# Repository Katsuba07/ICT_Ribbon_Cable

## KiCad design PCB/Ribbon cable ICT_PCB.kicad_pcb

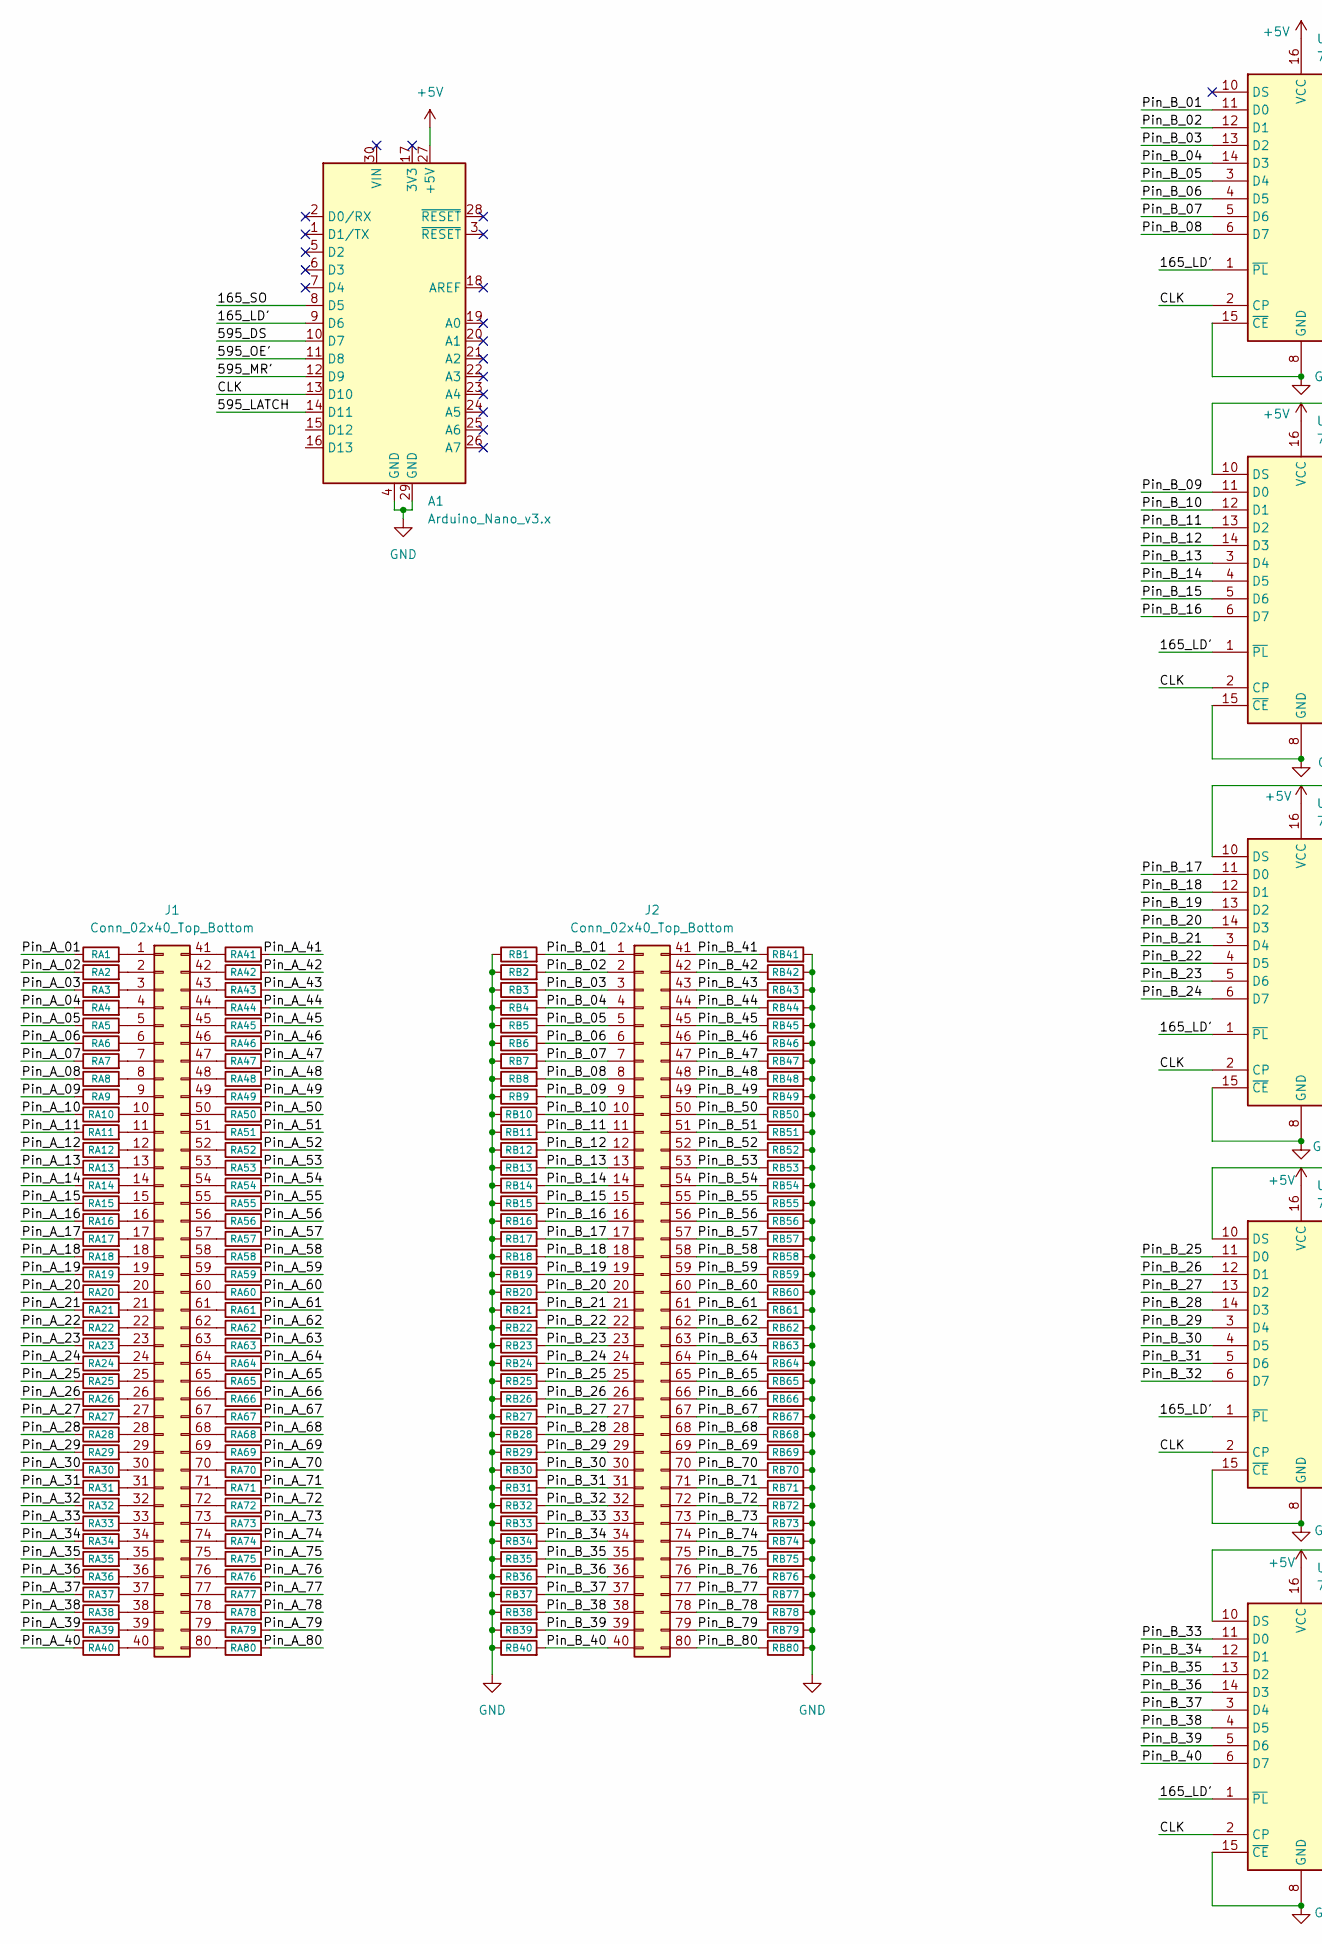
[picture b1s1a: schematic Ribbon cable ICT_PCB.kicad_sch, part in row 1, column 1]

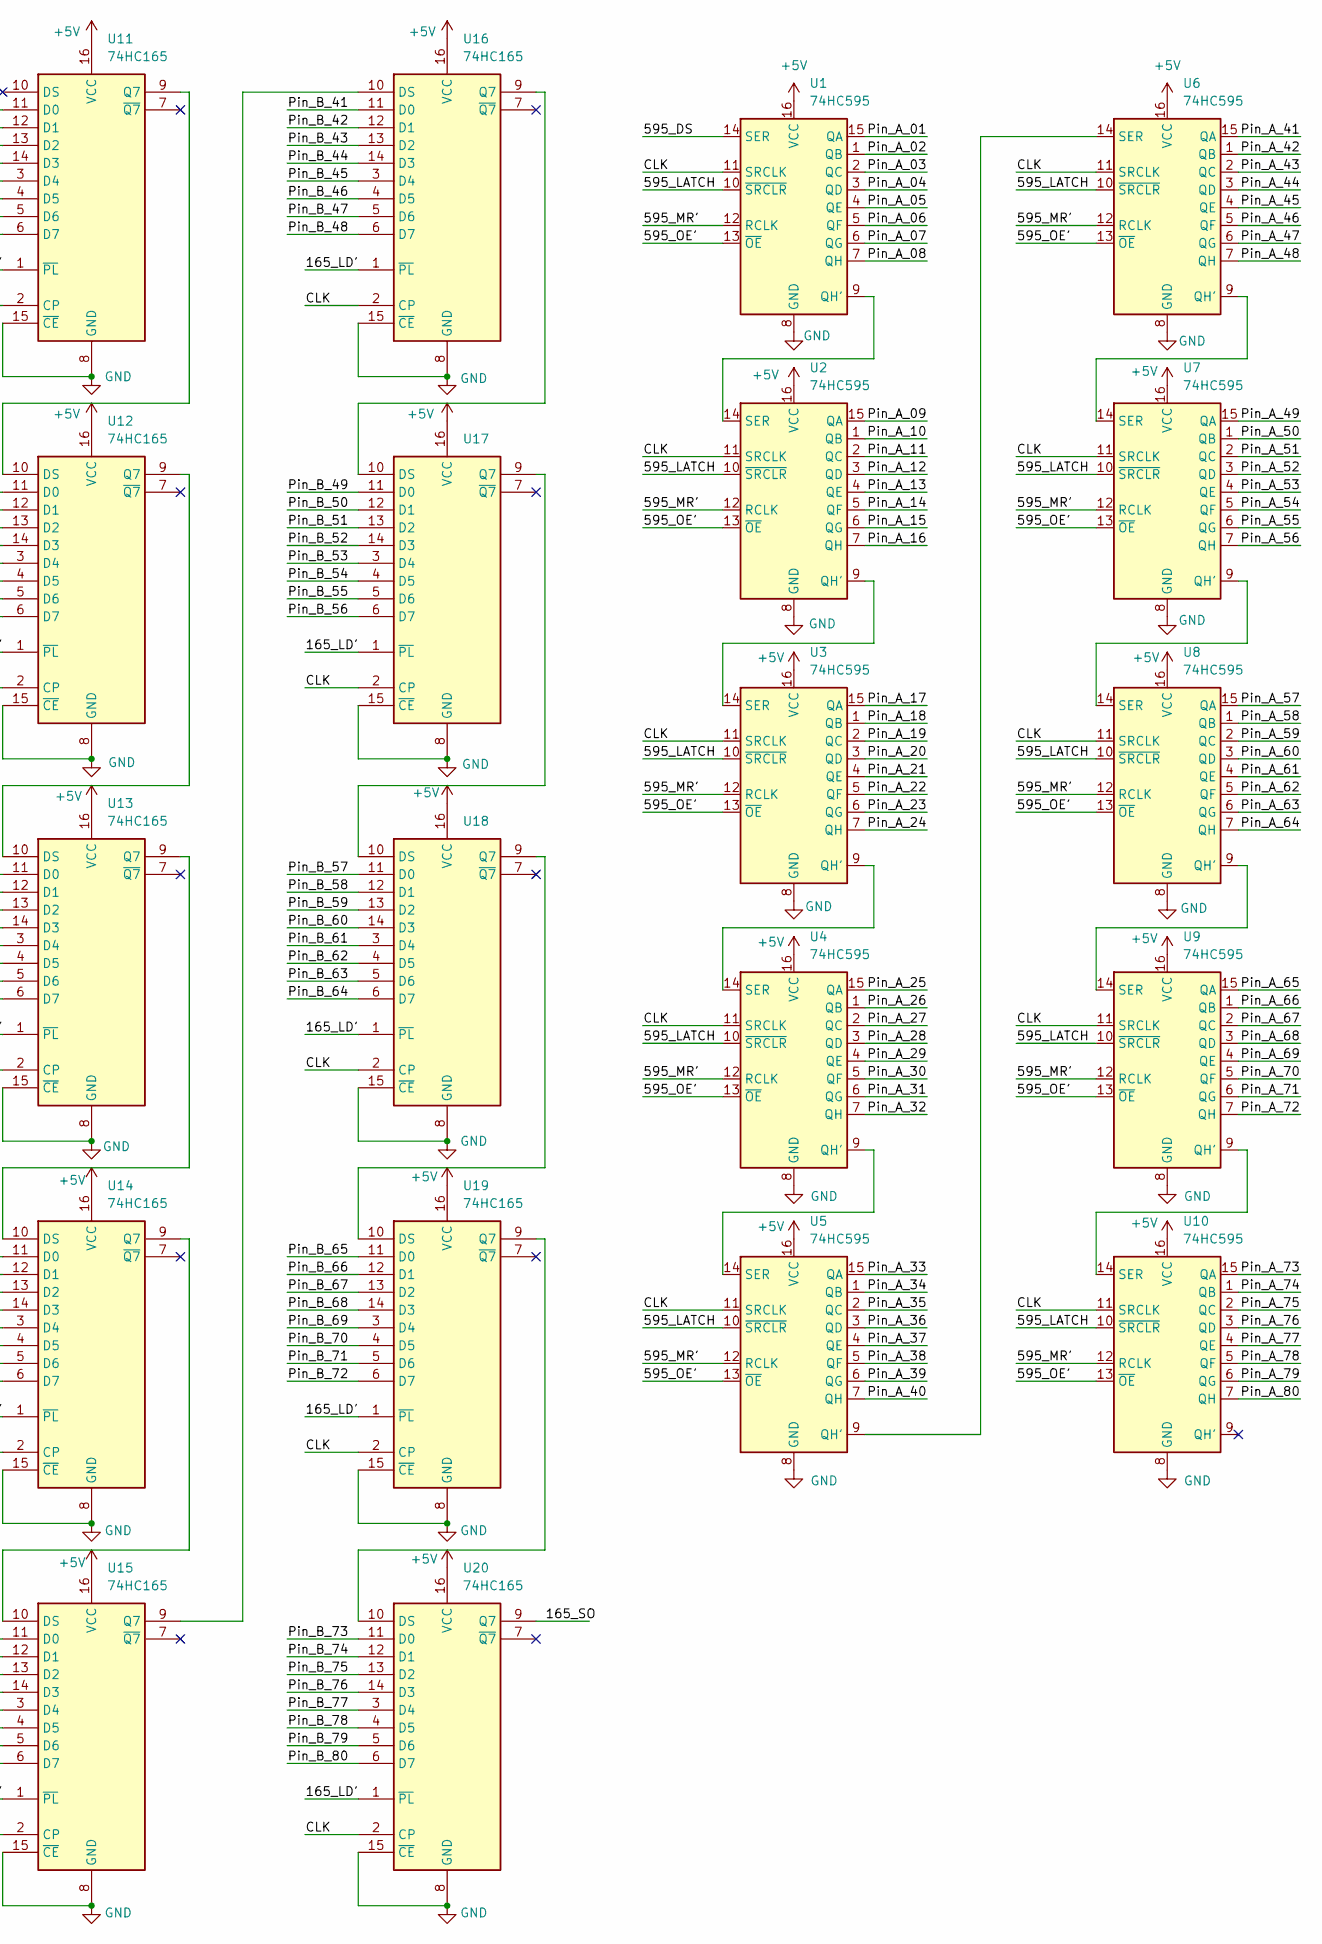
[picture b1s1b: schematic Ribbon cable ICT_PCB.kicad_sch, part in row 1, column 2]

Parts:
A1: Arduino_Nano_v3.x; Arduino_Nano
J1, J2: Conn_02x40_Top_Bottom; PinSocket_2x40_P2.54mm_Vertical
RA1, RA2, RA3, RA4, RA5, RA6, RA7, RA8, RA9, RA10, RA11, RA12, RA13, RA14, RA15, RA16, RA17, RA18, RA19, RA20, RA21, RA22, RA23, RA24, RA25, RA26, RA27, RA28, RA29, RA30, RA31, RA32, RA33, RA34, RA35, RA36, RA37, RA38, RA39, RA40, RA41, RA42, RA43, RA44, RA45, RA46, RA47, RA48, RA49, RA50, RA51, RA52, RA53, RA54, RA55, RA56, RA57, RA58, RA59, RA60, RA61, RA62, RA63, RA64, RA65, RA66, RA67, RA68, RA69, RA70, RA71, RA72, RA73, RA74, RA75, RA76, RA77, RA78, RA79, RA80: R; R_0603_1608Metric
RB1, RB2, RB3, RB4, RB5, RB6, RB7, RB8, RB9, RB10, RB11, RB12, RB13, RB14, RB15, RB16, RB17, RB18, RB19, RB20, RB21, RB22, RB23, RB24, RB25, RB26, RB27, RB28, RB29, RB30, RB31, RB32, RB33, RB34, RB35, RB36, RB37, RB38, RB39, RB40, RB41, RB42, RB43, RB44, RB45, RB46, RB47, RB48, RB49, RB50, RB51, RB52, RB53, RB54, RB55, RB56, RB57, RB58, RB59, RB60, RB61, RB62, RB63, RB64, RB65, RB66, RB67, RB68, RB69, RB70, RB71, RB72, RB73, RB74, RB75, RB76, RB77, RB78, RB79, RB80: R; R_0603_1608Metric
U1, U2, U3, U4, U5, U6, U7, U8, U9, U10: 74HC595; SOIC-16_3.9x9.9mm_P1.27mm
U11, U12, U13, U14, U15, U16, U17, U18, U19, U20: 74HC165; SOIC-16_3.9x9.9mm_P1.27mm

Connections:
+5V: A1.27 (+5V), U1.16 (VCC), U2.16 (VCC), U3.16 (VCC), U4.16 (VCC), U5.16 (VCC), U6.16 (VCC), U7.16 (VCC), U8.16 (VCC), U9.16 (VCC), U10.16 (VCC), U11.16 (VCC), U12.16 (VCC), U13.16 (VCC), U14.16 (VCC), U15.16 (VCC), U16.16 (VCC), U17.16 (VCC), U18.16 (VCC), U19.16 (VCC), U20.16 (VCC)
/165_LD': A1.9 (D6), U11.1 (~PL), U12.1 (~PL), U13.1 (~PL), U14.1 (~PL), U15.1 (~PL), U16.1 (~PL), U17.1 (~PL), U18.1 (~PL), U19.1 (~PL), U20.1 (~PL)
/165_SO: A1.8 (D5), U20.9 (Q7)
/595_DS: A1.10 (D7), U1.14 (SER)
/595_LATCH: A1.14 (D11), U1.10 (~SRCLR), U2.10 (~SRCLR), U3.10 (~SRCLR), U4.10 (~SRCLR), U5.10 (~SRCLR), U6.10 (~SRCLR), U7.10 (~SRCLR), U8.10 (~SRCLR), U9.10 (~SRCLR), U10.10 (~SRCLR)
/595_MR': A1.12 (D9), U1.12 (RCLK), U2.12 (RCLK), U3.12 (RCLK), U4.12 (RCLK), U5.12 (RCLK), U6.12 (RCLK), U7.12 (RCLK), U8.12 (RCLK), U9.12 (RCLK), U10.12 (RCLK)
/595_OE': A1.11 (D8), U1.13 (~OE), U2.13 (~OE), U3.13 (~OE), U4.13 (~OE), U5.13 (~OE), U6.13 (~OE), U7.13 (~OE), U8.13 (~OE), U9.13 (~OE), U10.13 (~OE)
/CLK: A1.13 (D10), U1.11 (SRCLK), U2.11 (SRCLK), U3.11 (SRCLK), U4.11 (SRCLK), U5.11 (SRCLK), U6.11 (SRCLK), U7.11 (SRCLK), U8.11 (SRCLK), U9.11 (SRCLK), U10.11 (SRCLK), U11.2 (CP), U12.2 (CP), U13.2 (CP), U14.2 (CP), U15.2 (CP), U16.2 (CP), U17.2 (CP), U18.2 (CP), U19.2 (CP), U20.2 (CP)
/Pin_A_01: RA1.1, U1.15 (QA)
/Pin_A_02: RA2.1, U1.1 (QB)
/Pin_A_03: RA3.1, U1.2 (QC)
/Pin_A_04: RA4.1, U1.3 (QD)
/Pin_A_05: RA5.1, U1.4 (QE)
/Pin_A_06: RA6.1, U1.5 (QF)
/Pin_A_07: RA7.1, U1.6 (QG)
/Pin_A_08: RA8.1, U1.7 (QH)
/Pin_A_09: RA9.1, U2.15 (QA)
/Pin_A_10: RA10.1, U2.1 (QB)
/Pin_A_11: RA11.1, U2.2 (QC)
/Pin_A_12: RA12.1, U2.3 (QD)
/Pin_A_13: RA13.1, U2.4 (QE)
/Pin_A_14: RA14.1, U2.5 (QF)
/Pin_A_15: RA15.1, U2.6 (QG)
/Pin_A_16: RA16.1, U2.7 (QH)
/Pin_A_17: RA17.1, U3.15 (QA)
/Pin_A_18: RA18.1, U3.1 (QB)
/Pin_A_19: RA19.1, U3.2 (QC)
/Pin_A_20: RA20.1, U3.3 (QD)
/Pin_A_21: RA21.1, U3.4 (QE)
/Pin_A_22: RA22.1, U3.5 (QF)
/Pin_A_23: RA23.1, U3.6 (QG)
/Pin_A_24: RA24.1, U3.7 (QH)
/Pin_A_25: RA25.1, U4.15 (QA)
/Pin_A_26: RA26.1, U4.1 (QB)
/Pin_A_27: RA27.1, U4.2 (QC)
/Pin_A_28: RA28.1, U4.3 (QD)
/Pin_A_29: RA29.1, U4.4 (QE)
/Pin_A_30: RA30.1, U4.5 (QF)
/Pin_A_31: RA31.1, U4.6 (QG)
/Pin_A_32: RA32.1, U4.7 (QH)
/Pin_A_33: RA33.1, U5.15 (QA)
/Pin_A_34: RA34.1, U5.1 (QB)
/Pin_A_35: RA35.1, U5.2 (QC)
/Pin_A_36: RA36.1, U5.3 (QD)
/Pin_A_37: RA37.1, U5.4 (QE)
/Pin_A_38: RA38.1, U5.5 (QF)
/Pin_A_39: RA39.1, U5.6 (QG)
/Pin_A_40: RA40.1, U5.7 (QH)
/Pin_A_41: RA41.2, U6.15 (QA)
/Pin_A_42: RA42.2, U6.1 (QB)
/Pin_A_43: RA43.2, U6.2 (QC)
/Pin_A_44: RA44.2, U6.3 (QD)
/Pin_A_45: RA45.2, U6.4 (QE)
/Pin_A_46: RA46.2, U6.5 (QF)
/Pin_A_47: RA47.2, U6.6 (QG)
/Pin_A_48: RA48.2, U6.7 (QH)
/Pin_A_49: RA49.2, U7.15 (QA)
/Pin_A_50: RA50.2, U7.1 (QB)
/Pin_A_51: RA51.2, U7.2 (QC)
/Pin_A_52: RA52.2, U7.3 (QD)
/Pin_A_53: RA53.2, U7.4 (QE)
/Pin_A_54: RA54.2, U7.5 (QF)
/Pin_A_55: RA55.2, U7.6 (QG)
/Pin_A_56: RA56.2, U7.7 (QH)
/Pin_A_57: RA57.2, U8.15 (QA)
/Pin_A_58: RA58.2, U8.1 (QB)
/Pin_A_59: RA59.2, U8.2 (QC)
/Pin_A_60: RA60.2, U8.3 (QD)
/Pin_A_61: RA61.2, U8.4 (QE)
/Pin_A_62: RA62.2, U8.5 (QF)
/Pin_A_63: RA63.2, U8.6 (QG)
/Pin_A_64: RA64.2, U8.7 (QH)
/Pin_A_65: RA65.2, U9.15 (QA)
/Pin_A_66: RA66.2, U9.1 (QB)
/Pin_A_67: RA67.2, U9.2 (QC)
/Pin_A_68: RA68.2, U9.3 (QD)
/Pin_A_69: RA69.2, U9.4 (QE)
/Pin_A_70: RA70.2, U9.5 (QF)
/Pin_A_71: RA71.2, U9.6 (QG)
/Pin_A_72: RA72.2, U9.7 (QH)
/Pin_A_73: RA73.2, U10.15 (QA)
/Pin_A_74: RA74.2, U10.1 (QB)
/Pin_A_75: RA75.2, U10.2 (QC)
/Pin_A_76: RA76.2, U10.3 (QD)
/Pin_A_77: RA77.2, U10.4 (QE)
/Pin_A_78: RA78.2, U10.5 (QF)
/Pin_A_79: RA79.2, U10.6 (QG)
/Pin_A_80: RA80.2, U10.7 (QH)
/Pin_B_01: J2.1, RB1.2, U11.11 (D0)
/Pin_B_02: J2.2, RB2.2, U11.12 (D1)
/Pin_B_03: J2.3, RB3.2, U11.13 (D2)
/Pin_B_04: J2.4, RB4.2, U11.14 (D3)
/Pin_B_05: J2.5, RB5.2, U11.3 (D4)
/Pin_B_06: J2.6, RB6.2, U11.4 (D5)
/Pin_B_07: J2.7, RB7.2, U11.5 (D6)
/Pin_B_08: J2.8, RB8.2, U11.6 (D7)
/Pin_B_09: J2.9, RB9.2, U12.11 (D0)
/Pin_B_10: J2.10, RB10.2, U12.12 (D1)
/Pin_B_11: J2.11, RB11.2, U12.13 (D2)
/Pin_B_12: J2.12, RB12.2, U12.14 (D3)
/Pin_B_13: J2.13, RB13.2, U12.3 (D4)
/Pin_B_14: J2.14, RB14.2, U12.4 (D5)
/Pin_B_15: J2.15, RB15.2, U12.5 (D6)
/Pin_B_16: J2.16, RB16.2, U12.6 (D7)
/Pin_B_17: J2.17, RB17.2, U13.11 (D0)
/Pin_B_18: J2.18, RB18.2, U13.12 (D1)
/Pin_B_19: J2.19, RB19.2, U13.13 (D2)
/Pin_B_20: J2.20, RB20.2, U13.14 (D3)
/Pin_B_21: J2.21, RB21.2, U13.3 (D4)
/Pin_B_22: J2.22, RB22.2, U13.4 (D5)
/Pin_B_23: J2.23, RB23.2, U13.5 (D6)
/Pin_B_24: J2.24, RB24.2, U13.6 (D7)
/Pin_B_25: J2.25, RB25.2, U14.11 (D0)
/Pin_B_26: J2.26, RB26.2, U14.12 (D1)
/Pin_B_27: J2.27, RB27.2, U14.13 (D2)
/Pin_B_28: J2.28, RB28.2, U14.14 (D3)
/Pin_B_29: J2.29, RB29.2, U14.3 (D4)
/Pin_B_30: J2.30, RB30.2, U14.4 (D5)
/Pin_B_31: J2.31, RB31.2, U14.5 (D6)
/Pin_B_32: J2.32, RB32.2, U14.6 (D7)
/Pin_B_33: J2.33, RB33.2, U15.11 (D0)
/Pin_B_34: J2.34, RB34.2, U15.12 (D1)
/Pin_B_35: J2.35, RB35.2, U15.13 (D2)
/Pin_B_36: J2.36, RB36.2, U15.14 (D3)
/Pin_B_37: J2.37, RB37.2, U15.3 (D4)
/Pin_B_38: J2.38, RB38.2, U15.4 (D5)
/Pin_B_39: J2.39, RB39.2, U15.5 (D6)
/Pin_B_40: J2.40, RB40.2, U15.6 (D7)
/Pin_B_41: J2.41, RB41.1, U16.11 (D0)
/Pin_B_42: J2.42, RB42.1, U16.12 (D1)
/Pin_B_43: J2.43, RB43.1, U16.13 (D2)
/Pin_B_44: J2.44, RB44.1, U16.14 (D3)
/Pin_B_45: J2.45, RB45.1, U16.3 (D4)
/Pin_B_46: J2.46, RB46.1, U16.4 (D5)
/Pin_B_47: J2.47, RB47.1, U16.5 (D6)
/Pin_B_48: J2.48, RB48.1, U16.6 (D7)
/Pin_B_49: J2.49, RB49.1, U17.11 (D0)
/Pin_B_50: J2.50, RB50.1, U17.12 (D1)
/Pin_B_51: J2.51, RB51.1, U17.13 (D2)
/Pin_B_52: J2.52, RB52.1, U17.14 (D3)
/Pin_B_53: J2.53, RB53.1, U17.3 (D4)
/Pin_B_54: J2.54, RB54.1, U17.4 (D5)
/Pin_B_55: J2.55, RB55.1, U17.5 (D6)
/Pin_B_56: J2.56, RB56.1, U17.6 (D7)
/Pin_B_57: J2.57, RB57.1, U18.11 (D0)
/Pin_B_58: J2.58, RB58.1, U18.12 (D1)
/Pin_B_59: J2.59, RB59.1, U18.13 (D2)
/Pin_B_60: J2.60, RB60.1, U18.14 (D3)
/Pin_B_61: J2.61, RB61.1, U18.3 (D4)
/Pin_B_62: J2.62, RB62.1, U18.4 (D5)
/Pin_B_63: J2.63, RB63.1, U18.5 (D6)
/Pin_B_64: J2.64, RB64.1, U18.6 (D7)
/Pin_B_65: J2.65, RB65.1, U19.11 (D0)
/Pin_B_66: J2.66, RB66.1, U19.12 (D1)
/Pin_B_67: J2.67, RB67.1, U19.13 (D2)
/Pin_B_68: J2.68, RB68.1, U19.14 (D3)
/Pin_B_69: J2.69, RB69.1, U19.3 (D4)
/Pin_B_70: J2.70, RB70.1, U19.4 (D5)
/Pin_B_71: J2.71, RB71.1, U19.5 (D6)
/Pin_B_72: J2.72, RB72.1, U19.6 (D7)
/Pin_B_73: J2.73, RB73.1, U20.11 (D0)
/Pin_B_74: J2.74, RB74.1, U20.12 (D1)
/Pin_B_75: J2.75, RB75.1, U20.13 (D2)
/Pin_B_76: J2.76, RB76.1, U20.14 (D3)
/Pin_B_77: J2.77, RB77.1, U20.3 (D4)
/Pin_B_78: J2.78, RB78.1, U20.4 (D5)
/Pin_B_79: J2.79, RB79.1, U20.5 (D6)
/Pin_B_80: J2.80, RB80.1, U20.6 (D7)
GND: A1.4 (GND), A1.29 (GND), RB1.1, RB2.1, RB3.1, RB4.1, RB5.1, RB6.1, RB7.1, RB8.1, RB9.1, RB10.1, RB11.1, RB12.1, RB13.1, RB14.1, RB15.1, RB16.1, RB17.1, RB18.1, RB19.1, RB20.1, RB21.1, RB22.1, RB23.1, RB24.1, RB25.1, RB26.1, RB27.1, RB28.1, RB29.1, RB30.1, RB31.1, RB32.1, RB33.1, RB34.1, RB35.1, RB36.1, RB37.1, RB38.1, RB39.1, RB40.1, RB41.2, RB42.2, RB43.2, RB44.2, RB45.2, RB46.2, RB47.2, RB48.2, RB49.2, RB50.2, RB51.2, RB52.2, RB53.2, RB54.2, RB55.2, RB56.2, RB57.2, RB58.2, RB59.2, RB60.2, RB61.2, RB62.2, RB63.2, RB64.2, RB65.2, RB66.2, RB67.2, RB68.2, RB69.2, RB70.2, RB71.2, RB72.2, RB73.2, RB74.2, RB75.2, RB76.2, RB77.2, RB78.2, RB79.2, RB80.2, U1.8 (GND), U2.8 (GND), U3.8 (GND), U4.8 (GND), U5.8 (GND), U6.8 (GND), U7.8 (GND), U8.8 (GND), U9.8 (GND), U10.8 (GND), U11.8 (GND), U11.15 (~CE), U12.8 (GND), U12.15 (~CE), U13.8 (GND), U13.15 (~CE), U14.8 (GND), U14.15 (~CE), U15.8 (GND), U15.15 (~CE), U16.8 (GND), U16.15 (~CE), U17.8 (GND), U17.15 (~CE), U18.8 (GND), U18.15 (~CE), U19.8 (GND), U19.15 (~CE), U20.8 (GND), U20.15 (~CE)
unnamed: J1.1, RA1.2
unnamed: J1.2, RA2.2
unnamed: J1.3, RA3.2
unnamed: J1.4, RA4.2
unnamed: J1.5, RA5.2
unnamed: J1.6, RA6.2
unnamed: J1.7, RA7.2
unnamed: J1.8, RA8.2
unnamed: J1.9, RA9.2
unnamed: J1.10, RA10.2
unnamed: J1.11, RA11.2
unnamed: J1.12, RA12.2
unnamed: J1.13, RA13.2
unnamed: J1.14, RA14.2
unnamed: J1.15, RA15.2
unnamed: J1.16, RA16.2
unnamed: J1.17, RA17.2
unnamed: J1.18, RA18.2
unnamed: J1.19, RA19.2
unnamed: J1.20, RA20.2
unnamed: J1.21, RA21.2
unnamed: J1.22, RA22.2
unnamed: J1.23, RA23.2
unnamed: J1.24, RA24.2
unnamed: J1.25, RA25.2
unnamed: J1.26, RA26.2
unnamed: J1.27, RA27.2
unnamed: J1.28, RA28.2
unnamed: J1.29, RA29.2
unnamed: J1.30, RA30.2
unnamed: J1.31, RA31.2
unnamed: J1.32, RA32.2
unnamed: J1.33, RA33.2
unnamed: J1.34, RA34.2
unnamed: J1.35, RA35.2
unnamed: J1.36, RA36.2
unnamed: J1.37, RA37.2
unnamed: J1.38, RA38.2
unnamed: J1.39, RA39.2
unnamed: J1.40, RA40.2
unnamed: J1.41, RA41.1
unnamed: J1.42, RA42.1
unnamed: J1.43, RA43.1
unnamed: J1.44, RA44.1
unnamed: J1.45, RA45.1
unnamed: J1.46, RA46.1
unnamed: J1.47, RA47.1
unnamed: J1.48, RA48.1
unnamed: J1.49, RA49.1
unnamed: J1.50, RA50.1
unnamed: J1.51, RA51.1
unnamed: J1.52, RA52.1
unnamed: J1.53, RA53.1
unnamed: J1.54, RA54.1
unnamed: J1.55, RA55.1
unnamed: J1.56, RA56.1
unnamed: J1.57, RA57.1
unnamed: J1.58, RA58.1
unnamed: J1.59, RA59.1
unnamed: J1.60, RA60.1
unnamed: J1.61, RA61.1
unnamed: J1.62, RA62.1
unnamed: J1.63, RA63.1
unnamed: J1.64, RA64.1
unnamed: J1.65, RA65.1
unnamed: J1.66, RA66.1
unnamed: J1.67, RA67.1
unnamed: J1.68, RA68.1
unnamed: J1.69, RA69.1
unnamed: J1.70, RA70.1
unnamed: J1.71, RA71.1
unnamed: J1.72, RA72.1
unnamed: J1.73, RA73.1
unnamed: J1.74, RA74.1
unnamed: J1.75, RA75.1
unnamed: J1.76, RA76.1
unnamed: J1.77, RA77.1
unnamed: J1.78, RA78.1
unnamed: J1.79, RA79.1
unnamed: J1.80, RA80.1
unnamed: U1.9 (QH'), U2.14 (SER)
unnamed: U2.9 (QH'), U3.14 (SER)
unnamed: U3.9 (QH'), U4.14 (SER)
unnamed: U4.9 (QH'), U5.14 (SER)
unnamed: U5.9 (QH'), U6.14 (SER)
unnamed: U6.9 (QH'), U7.14 (SER)
unnamed: U7.9 (QH'), U8.14 (SER)
unnamed: U8.9 (QH'), U9.14 (SER)
unnamed: U9.9 (QH'), U10.14 (SER)
unnamed: U11.9 (Q7), U12.10 (DS)
unnamed: U12.9 (Q7), U13.10 (DS)
unnamed: U13.9 (Q7), U14.10 (DS)
unnamed: U14.9 (Q7), U15.10 (DS)
unnamed: U15.9 (Q7), U16.10 (DS)
unnamed: U16.9 (Q7), U17.10 (DS)
unnamed: U17.9 (Q7), U18.10 (DS)
unnamed: U18.9 (Q7), U19.10 (DS)
unnamed: U19.9 (Q7), U20.10 (DS)

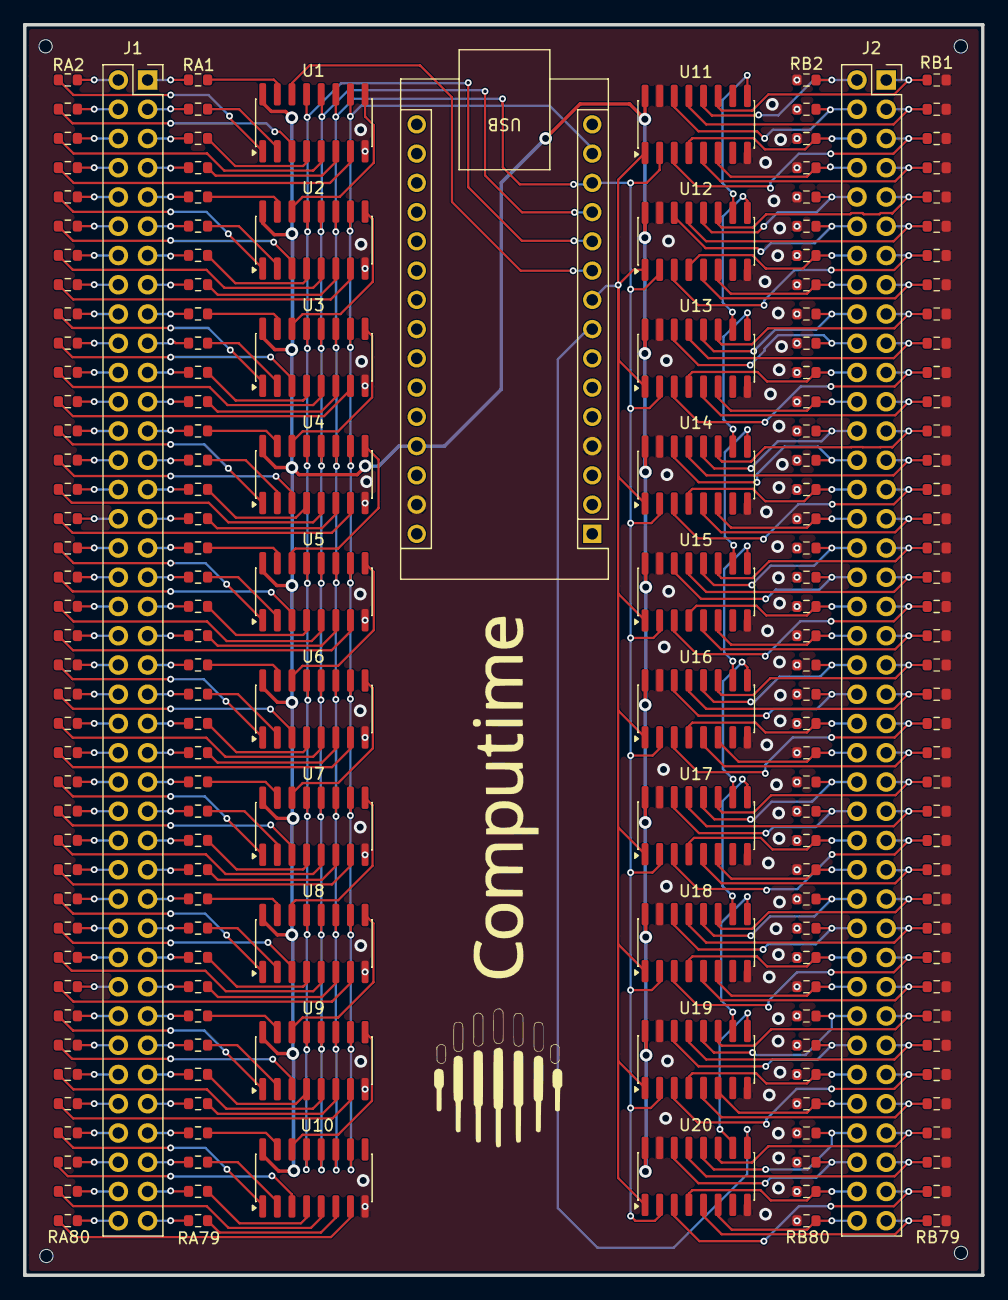
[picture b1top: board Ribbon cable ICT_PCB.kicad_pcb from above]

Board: 2 copper layers, 83.2 x 108.6 mm, 183 parts (0 on the bottom side), 267 nets.
